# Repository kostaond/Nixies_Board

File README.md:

# Nixies_Board
This repository stores Nixie Clock PCB board and schematics created in Eagle. It also contains drawings and 3D model of the metal box. 

The design goal is to create a Nixie clocks driven by low-cost ARM processor with simple serial interface which is used for clock power down scenario remedy and for time synchronization. The actual solution for the time synchronization is up to the user and can be realized by e.g. Bluetooth or Wifi modules like Wemos D1.

Notes:
 - Power supply is based on https://threeneurons.wordpress.com/nixie-power-supply/
 - High voltage part of the design can be disabled by disconnecting JP2. This is handy for software debugging from the safety perspective.
 - I saw that a lot of people had an issue with ghosting when multiplexing the nixies. I was not an exception. The solution is to connect all cathodes to pre-bias voltage of 100V via e.g. 220K rezistors (check the schematics for more details).  Refer to Section "OFF CATHODE CHARACTERISTICS" at http://www.zapro.dk/public/PDF/nixie/N101.pdf to find magic behind.

Two revisions exist in this repository – REV1 and REV2 (see tags). 
* The REV1 is the very first prototype where the wrong BCD decoder was used (74HC42 with active low output while BCD decoder with active high should have been used). This could be partially resolved by resoldering with 4028, external wiring and SW workaround. However DO NOT use this version!
* The REV2 fixes the issue with the BCD decoder, resolves ghosting and adds footprint preparation for Wemos D1 Wifi modul.

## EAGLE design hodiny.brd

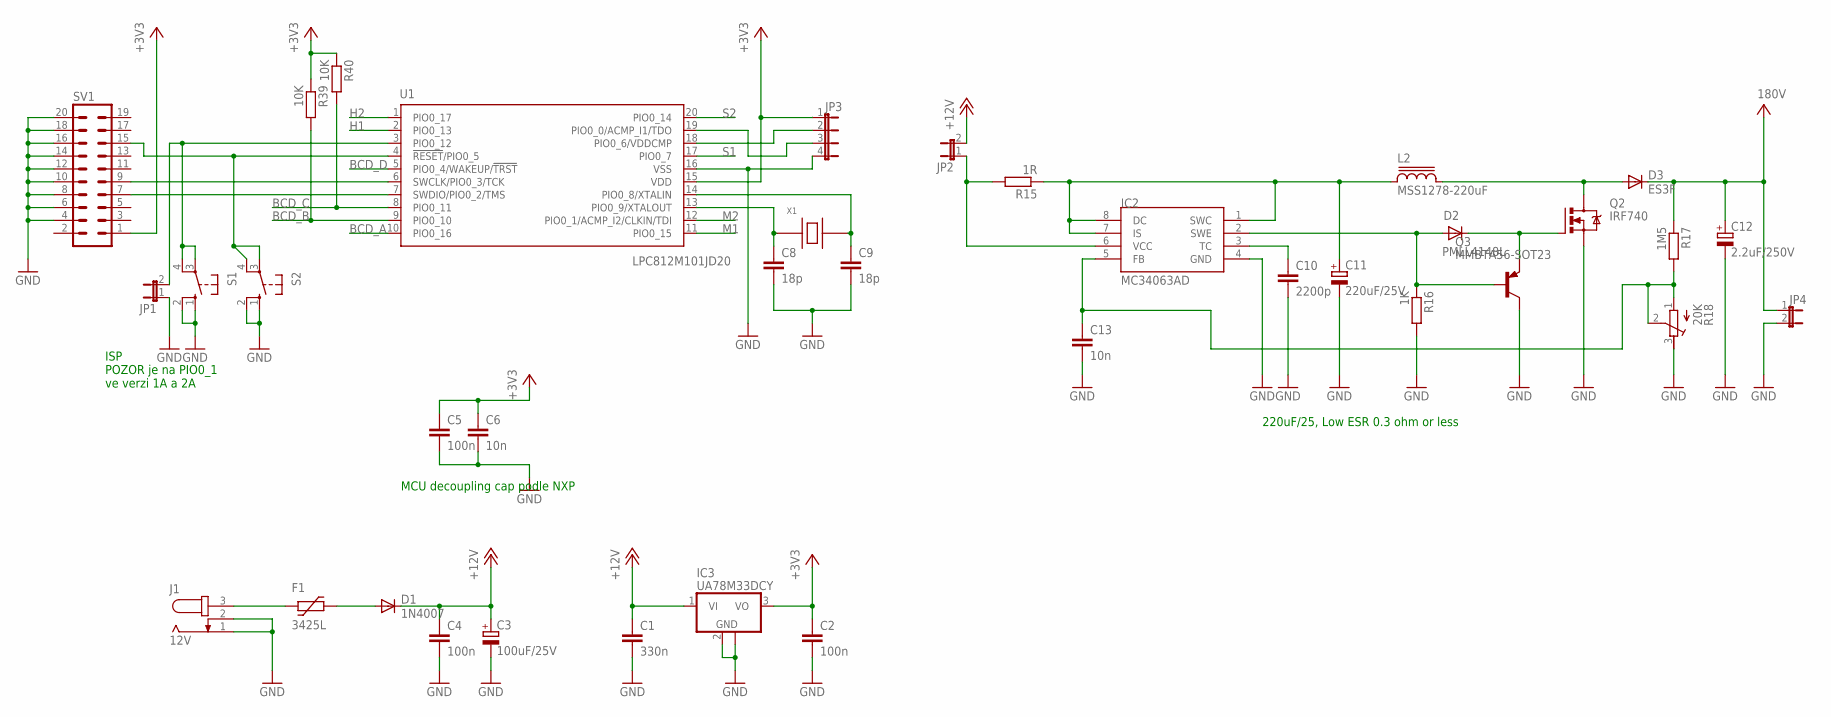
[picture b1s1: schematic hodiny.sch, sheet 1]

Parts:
C1: 330n; C1206
C2, C4, C5: 100n; C1206
C3: 100uF/25V; 153CLV-0605
C6, C13: 10n; C1206
C8, C9: 18p; C0805
C10: 2200p; C1206
C11: 220uF/25V; 153CLV-0605
C12: 2.2uF/250V; E2,5-6
D1: 1N4007; MELF-MLL41
D2: PMLL4148L; SOD80C
D3: ES3F; SMC
F1: 3425L
IC2: MC34063AD; SOIC8
IC3: UA78M33DCY; SOT223
J1: 12V; SPC4077
JP1, JP2, JP4: JP1E; JP1
JP3: JP4E; JP4
L2: MSS1278-220uF; MSS1278
Q2: IRF740; TO220BV
Q3: MMBTA56-SOT23; SOT23
R15: 1R; R1206
R16: 1K; R1206
R17: 1M5; R1206
R18: 20K; RTRIMTSM53YJ
R39, R40: 10K; R1206
S1, S2: 10-XX; B3F-10XX
SV1: ML20
U1: LPC812M101JD20; SOT163-1
X1: SMCE-5032; IQG5032B

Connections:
+3V3: C2.1, C5.1, C6.1, IC3.3 (VO), JP3.1, R39.1, R40.1, SV1.1, U1.15 (VDD); also elsewhere on the board
+12V: C1.1, C3.+, C4.1, D1.C, IC3.1 (VI), JP2.2
BCD_A: U1.10 (PIO0_16); also elsewhere on the board
BCD_B: R39.2, U1.9 (PIO0_10); also elsewhere on the board
BCD_C: R40.2, U1.8 (PIO0_11); also elsewhere on the board
BCD_D: U1.5 (PIO0_4/WAKEUP/!TRST!); also elsewhere on the board
GND: C1.2, C2.2, C3.-, C4.2, C5.2, C6.2, C8.2, C9.2, C10.2, C11.-, C12.-, C13.2, IC2.4 (GND), IC3.2 (GND), IC3.4 (GND), J1.1, J1.2, JP1.1, JP3.4, JP4.2, Q2.S, Q3.3 (C), R16.2, R18.3 (E), S1.1 (S), S1.2 (S1), S2.1 (S), S2.2 (S1), SV1.4, SV1.6, SV1.8, SV1.10, SV1.12, SV1.14, SV1.16, SV1.18, SV1.20, U1.16 (VSS); also elsewhere on the board
H1: U1.2 (PIO0_13); also elsewhere on the board
H2: U1.1 (PIO0_17); also elsewhere on the board
M1: U1.11 (PIO0_15); also elsewhere on the board
M2: U1.12 (PIO0_1/ACMP_I2/CLKIN/TDI); also elsewhere on the board
unnamed: F1.P$1 (1), J1.3
unnamed: D1.A, F1.P$2 (2)
unnamed: S2.3, S2.4 (P1), SV1.15, U1.4 (!RESET!/PIO0_5)
unnamed: JP1.2, S1.3, S1.4 (P1), U1.3 (PIO0_12)
unnamed: SV1.9, U1.6 (SWCLK/PIO0_3/TCK)
unnamed: SV1.7, U1.7 (SWDIO/PIO0_2/TMS)
unnamed: C9.1, U1.14 (PIO0_8/XTALIN), X1.3 (PIN2)
unnamed: C8.1, U1.13 (PIO0_9/XTALOUT), X1.1 (PIN1)
unnamed: JP3.2, U1.18 (PIO0_6/VDDCMP)
unnamed: JP3.3, U1.19 (PIO0_0/ACMP_I1/TDO)
unnamed: C11.+, IC2.1 (SWC), IC2.7 (IS), IC2.8 (DC), L2.1, R15.1
unnamed: C10.1, IC2.3 (TC)
unnamed: D2.1 (K), Q2.G, Q3.2 (E)
unnamed: D3.A, L2.2, Q2.D
unnamed: D2.2 (A), IC2.2 (SWE), Q3.1 (B), R16.1
unnamed: IC2.6 (VCC), JP2.1, R15.2
unnamed: C13.1, IC2.5 (FB), R17.2, R18.1 (A), R18.2 (S)
S1: U1.17 (PIO0_7); also elsewhere on the board
S2: U1.20 (PIO0_14); also elsewhere on the board
V+: C12.+, D3.C, JP4.1, R17.1; also elsewhere on the board

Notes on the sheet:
MCU decoupling cap podle NXP
ISP POZOR je na PIO0_1 ve verzi 1A a 2A
220uF/25, Low ESR 0.3 ohm or less

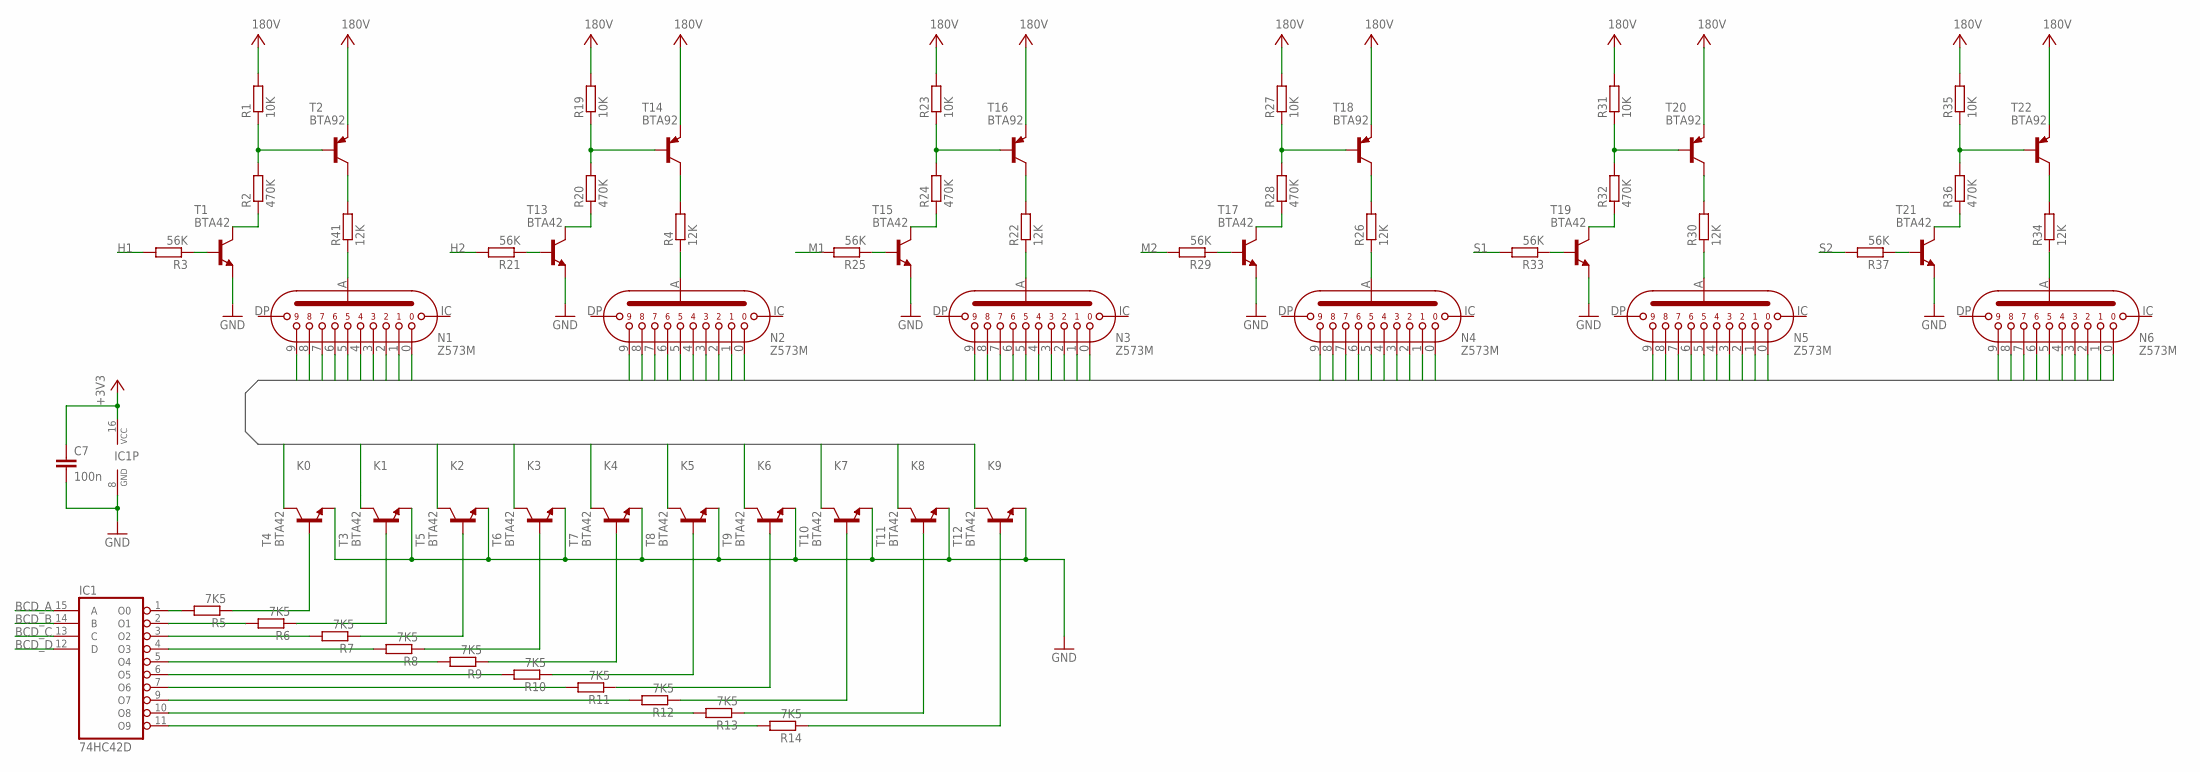
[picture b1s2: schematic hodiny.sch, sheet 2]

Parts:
C7: 100n; C1206
IC1: 74HC42D; SO16
N1, N2, N3, N4, N5, N6: Z573M; Z570M
R1, R19, R23, R27, R31, R35: 10K; R1206
R2, R20, R24, R28, R32, R36: 470K; R1206
R3, R21, R25, R29, R33, R37: 56K; R1206
R4, R22, R26, R30, R34, R41: 12K; 0207/7
R5, R6, R7, R8, R9, R10, R11, R12, R13, R14: 7K5; R1206
T1, T3, T4, T5, T6, T7, T8, T9, T10, T11, T12, T13, T15, T17, T19, T21: BTA42; SOT23-BEC
T2, T14, T16, T18, T20, T22: BTA92; SOT23-BEC

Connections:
+3V3: C7.1, IC1.16 (VCC); also elsewhere on the board
BCD_A: IC1.15 (A); also elsewhere on the board
BCD_B: IC1.14 (B); also elsewhere on the board
BCD_C: IC1.13 (C); also elsewhere on the board
BCD_D: IC1.12 (D); also elsewhere on the board
GND: C7.2, IC1.8 (GND), T1.E, T3.E, T4.E, T5.E, T6.E, T7.E, T8.E, T9.E, T10.E, T11.E, T12.E, T13.E, T15.E, T17.E, T19.E, T21.E; also elsewhere on the board
H1: R3.2; also elsewhere on the board
H2: R21.2; also elsewhere on the board
K0: N1.12 (0), N2.12 (0), N3.12 (0), N4.12 (0), N5.12 (0), N6.12 (0), T4.C
K1: N1.1, N2.1, N3.1, N4.1, N5.1, N6.1, T3.C
K2: N1.2, N2.2, N3.2, N4.2, N5.2, N6.2, T5.C
K3: N1.3, N2.3, N3.3, N4.3, N5.3, N6.3, T6.C
K4: N1.5 (4), N2.5 (4), N3.5 (4), N4.5 (4), N5.5 (4), N6.5 (4), T7.C
K5: N1.6 (5), N2.6 (5), N3.6 (5), N4.6 (5), N5.6 (5), N6.6 (5), T8.C
K6: N1.7 (6), N2.7 (6), N3.7 (6), N4.7 (6), N5.7 (6), N6.7 (6), T9.C
K7: N1.8 (7), N2.8 (7), N3.8 (7), N4.8 (7), N5.8 (7), N6.8 (7), T10.C
K8: N1.9 (8), N2.9 (8), N3.9 (8), N4.9 (8), N5.9 (8), N6.9 (8), T11.C
K9: N1.11 (9), N2.11 (9), N3.11 (9), N4.11 (9), N5.11 (9), N6.11 (9), T12.C
M1: R25.2; also elsewhere on the board
M2: R29.2; also elsewhere on the board
unnamed: R3.1, T1.B
unnamed: R2.1, T1.C
unnamed: R1.1, R2.2, T2.B
unnamed: R21.1, T13.B
unnamed: R41.2, T2.C
unnamed: IC1.1 (O0), R5.2
unnamed: N1.13 (A), R41.1
unnamed: IC1.2 (O1), R6.2
unnamed: IC1.3 (O2), R7.2
unnamed: IC1.4 (O3), R8.2
unnamed: IC1.5 (O4), R9.2
unnamed: IC1.6 (O5), R10.2
unnamed: IC1.7 (O6), R11.2
unnamed: IC1.9 (O7), R12.2
unnamed: IC1.10 (O8), R13.2
unnamed: IC1.11 (O9), R14.2
unnamed: R5.1, T4.B
unnamed: R6.1, T3.B
unnamed: R7.1, T5.B
unnamed: R8.1, T6.B
unnamed: R10.1, T8.B
unnamed: R11.1, T9.B
unnamed: R12.1, T10.B
unnamed: R13.1, T11.B
unnamed: R14.1, T12.B
unnamed: R9.1, T7.B
unnamed: R20.1, T13.C
unnamed: R19.1, R20.2, T14.B
unnamed: R4.2, T14.C
unnamed: N2.13 (A), R4.1
unnamed: R25.1, T15.B
unnamed: R24.1, T15.C
unnamed: R23.1, R24.2, T16.B
unnamed: R22.2, T16.C
unnamed: N3.13 (A), R22.1
unnamed: R29.1, T17.B
unnamed: R28.1, T17.C
unnamed: R27.1, R28.2, T18.B
unnamed: R26.2, T18.C
unnamed: N4.13 (A), R26.1
unnamed: R33.1, T19.B
unnamed: R32.1, T19.C
unnamed: R31.1, R32.2, T20.B
unnamed: R30.2, T20.C
unnamed: N5.13 (A), R30.1
unnamed: R37.1, T21.B
unnamed: R36.1, T21.C
unnamed: R35.1, R36.2, T22.B
unnamed: R34.2, T22.C
unnamed: N6.13 (A), R34.1
S1: R33.2; also elsewhere on the board
S2: R37.2; also elsewhere on the board
V+: R1.2, R19.2, R23.2, R27.2, R31.2, R35.2, T2.E, T14.E, T16.E, T18.E, T20.E, T22.E; also elsewhere on the board

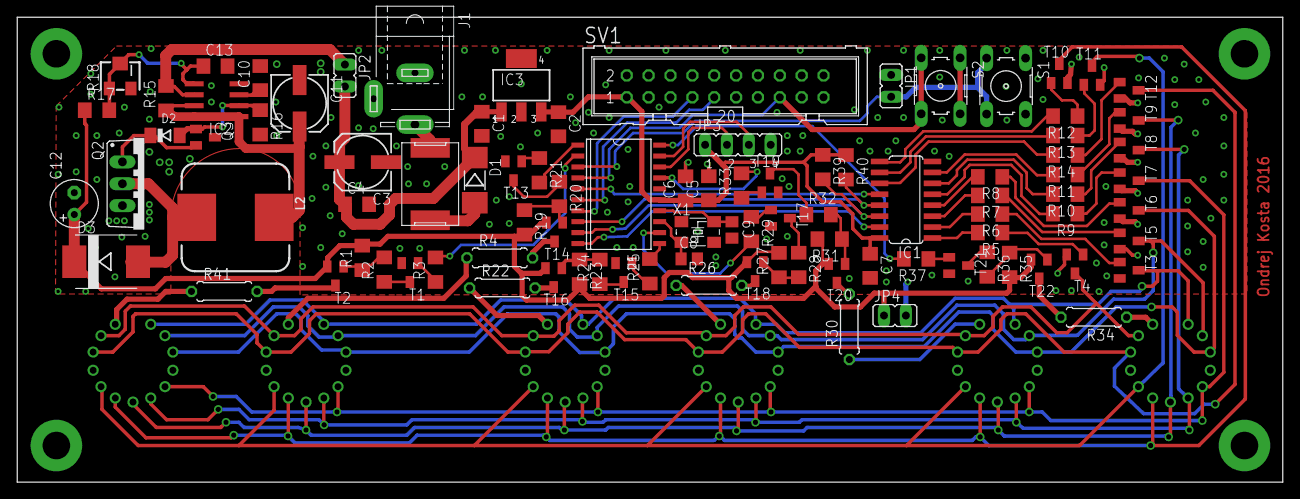
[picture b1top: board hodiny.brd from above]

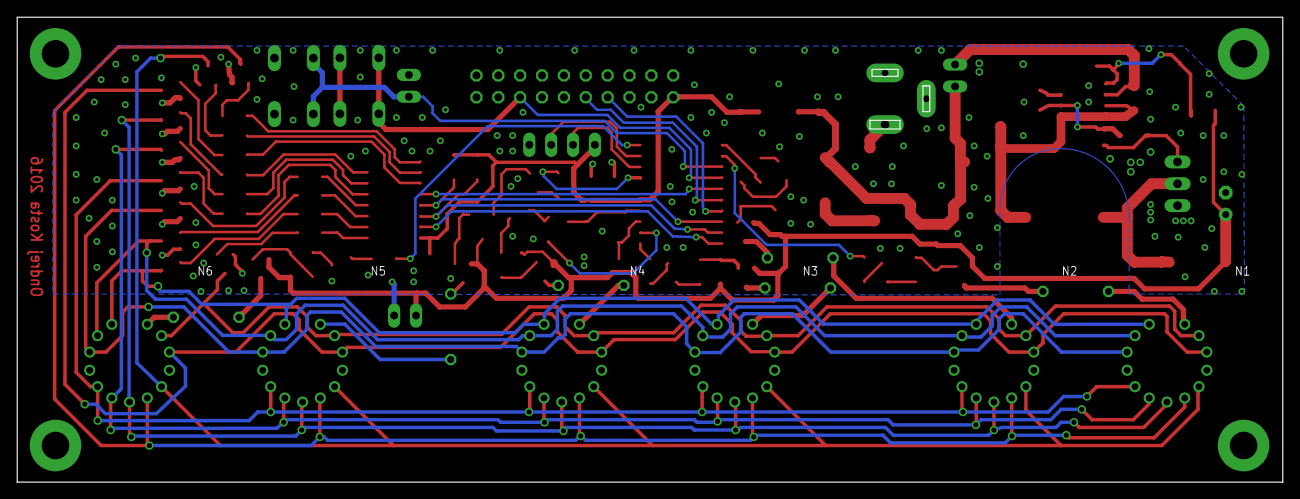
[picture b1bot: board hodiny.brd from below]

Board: 2 copper layers, 147.0 x 54.0 mm, 101 parts (6 on the bottom side), 91 nets.

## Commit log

2020-05-06 REV 1
2020-05-06 REV2 - Red Board
2020-10-25 Info about ghosting resolution added
2020-10-25 - renamed to English - PDF output
2020-10-29 Nixie Box
    Nixie box drawing, models and photo added.
2020-10-29 Update README.md
    Image added.
    Rev description.

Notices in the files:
parts and their libraries:
NXP_60_26022015: This library may be distributed and adapted freely for any purpose, as long as NXP is credited and any new creation is licensed under the same terms.
